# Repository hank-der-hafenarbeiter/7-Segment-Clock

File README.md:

7-Segment-Clock
===============

Schematic/PCB-Board for building a 4 digit seven segment display wall clock.

Both files were created using EAGLE 6.5.0, screenshots are available here: http://imgur.com/a/bXdcL

IMPORTANT:
I'm using the IRLML 6402 p-channel MOSFET in a SOT-23 package and a BFN 26 npn transistor also in SOT-23.  As of yet this is not changed in the schematics!

Greater picture:

This is a schematic/board i'll use to drive a ~80cm x ~50cm 7-segment digit on my wall. The display will use 12V RGB led strips with a power of ~7,2W/m. The board will make it possible to drive the 12V@180mA one segmetn needs from an ordinary arduino pin.

The "SEG#" pins will be connected to the kathode side of the strip while the anode side will be connected to the RGB led driver. The "PIN#" pins will be connected to the digital pins of an Arduino Mega. I will use the PWM pins to connect to the LED driver.

In the end i'll use 4 of these boards two drive for digits to make a wall clock.

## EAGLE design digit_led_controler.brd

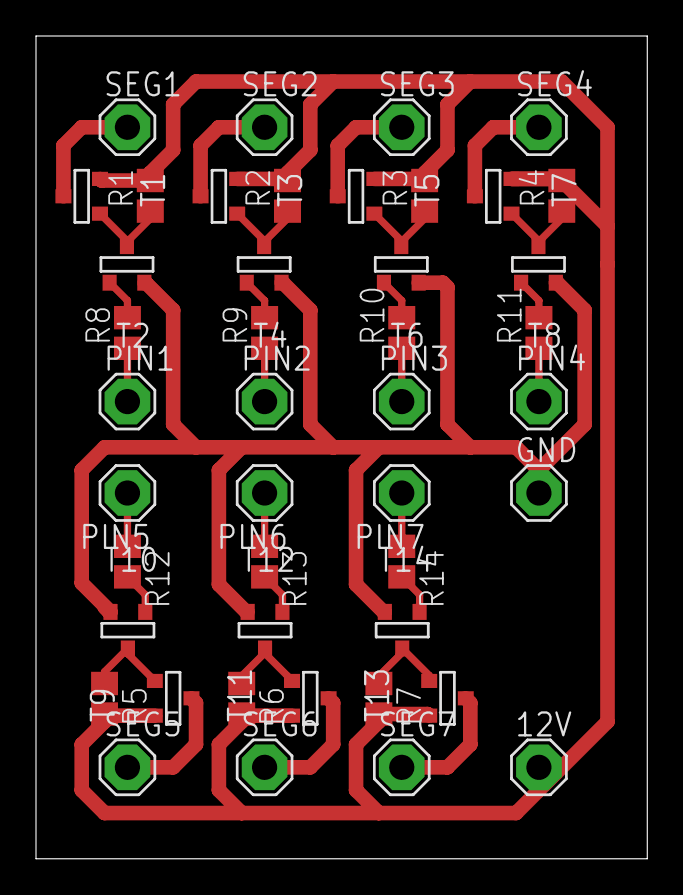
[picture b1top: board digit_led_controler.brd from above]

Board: 2 copper layers, 34.0 x 45.7 mm, 44 parts (0 on the bottom side), 30 nets.

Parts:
12V: SE14
GND: SE14
PIN1, PIN2, PIN3, PIN4, PIN5, PIN6, PIN7: SE14
R1, R2, R3, R4, R5, R6, R7, R8, R9, R10, R11, R12, R13, R14: R0805
SEG1, SEG2, SEG3, SEG4, SEG5, SEG6, SEG7: SE14
T1, T2, T3, T4, T5, T6, T7, T8, T9, T10, T11, T12, T13, T14: SOT-23

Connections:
unnamed: PIN1.MP, R8.1
unnamed: R1.1, T1.3, T2.1
unnamed: GND.MP, T2.2, T4.2, T6.2, T8.2, T10.2, T12.2, T14.2
unnamed: SEG1.MP, T1.1
unnamed: R2.1, T3.3, T4.1
unnamed: 12V.MP, R1.2, R2.2, R3.2, R4.2, R5.2, R6.2, R7.2, T1.2, T3.2, T5.2, T7.2, T9.2, T11.2, T13.2
unnamed: PIN2.MP, R9.1
unnamed: PIN3.MP, R10.1
unnamed: PIN4.MP, R11.1
unnamed: SEG2.MP, T3.1
unnamed: PIN5.MP, R12.1
unnamed: PIN6.MP, R13.1
unnamed: R3.1, T5.3, T6.1
unnamed: PIN7.MP, R14.1
unnamed: R8.2, T2.3
unnamed: R9.2, T4.3
unnamed: SEG3.MP, T5.1
unnamed: R10.2, T6.3
unnamed: R11.2, T8.3
unnamed: R12.2, T10.3
unnamed: R13.2, T12.3
unnamed: R4.1, T7.3, T8.1
unnamed: R14.2, T14.3
unnamed: SEG4.MP, T7.1
unnamed: R5.1, T9.3, T10.1
unnamed: SEG5.MP, T9.1
unnamed: R6.1, T11.3, T12.1
unnamed: SEG6.MP, T11.1
unnamed: R7.1, T13.3, T14.1
unnamed: SEG7.MP, T13.1

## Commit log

2014-12-13 holes in corners
    new schematics
